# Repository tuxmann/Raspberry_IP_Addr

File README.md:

# Raspberry Pi IP Address Display

A hardware add-on that displays your Raspberry Pi's IP address on a 3-digit 7-segment LED display. Compatible with all Raspberry Pi models and other pin-compatible SBCs (Orange Pi, Banana Pi, Odroid, etc.).

## Quick Start

1. **Enable I2C and SPI:** `sudo raspi-config` → Interface Options
2. **Install:** `sudo apt install python3-smbus i2c-tools` (or `pip install smbus2`)
3. **Run:** `python3 hostip.py`
4. **Auto-start at boot:** `./deploy-to-pi.sh --install-service` (after deploying)

See **[docs/SETUP.md](docs/SETUP.md)** for the full setup guide, including ATtiny88 programming and the reset pin requirement.

## Hardware

- **Board:** ATtiny88 drives a 3-digit ELT-316 common-anode 7-segment display
- **Communication:** I2C at address 0x5A
- **Size:** Sits 0.6" (1.5cm) above the Pi; total height ~1" (2.5cm) with headers
- **Expansion:** P3 (left) and P4 (right) connectors bring out Port C & D (ADC, analog comparator, external interrupts)

## Features

- Power-on message ("rPI IP by JAY v1.1 GPL 3")
- Timeout message if no IP received within ~5 minutes
- Cycles through IP octets (e.g., 192 → 168 → 1 → 100)

## Climate node (DHT22, standalone)

The board can run **without a Pi** as a temperature/humidity display using a **DHT22** on header **P3 pin 1 (PC0)**.

- Firmware: [`climate-node-dht22/`](climate-node-dht22/)
- Setup, wiring, build, and flash: **[docs/CLIMATE_NODE.md](docs/CLIMATE_NODE.md)**

Shows °F (e.g. `78.3`) and humidity (e.g. `H38`), one sensor read every 6 seconds (3 s per value on the display). Optional photoresistor dimming on **P3 pin 2**; compile-time calibration offsets for temperature and humidity.

## Documentation

- [Setup Guide](docs/SETUP.md) — Pi IP display: installation, configuration, and flashing
- [Climate Node (DHT22)](docs/CLIMATE_NODE.md) — Standalone temp/humidity firmware
- [Releases](https://github.com/tuxmann/Raspberry_IP_Addr/releases) — Pre-built binaries and documents
- [Schematic](docs/Pi.IP.Addr.Schematic.pdf)

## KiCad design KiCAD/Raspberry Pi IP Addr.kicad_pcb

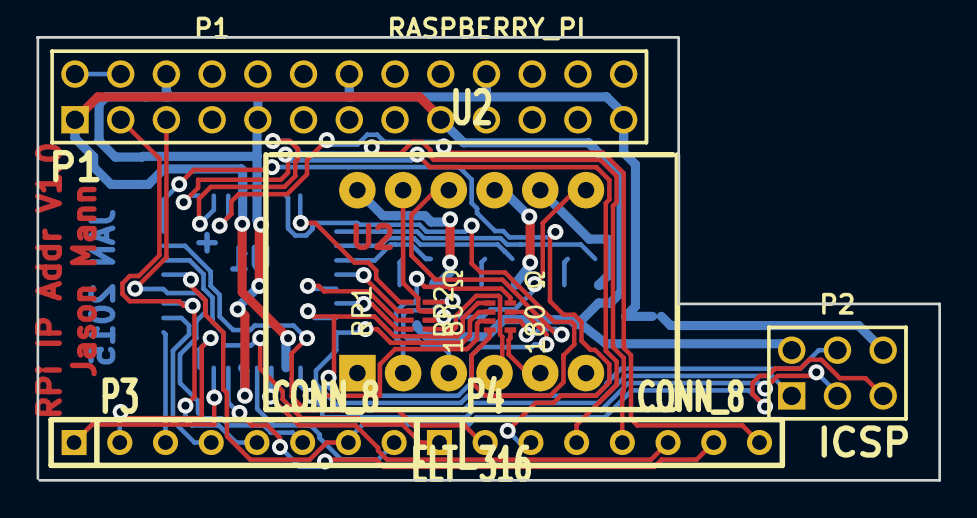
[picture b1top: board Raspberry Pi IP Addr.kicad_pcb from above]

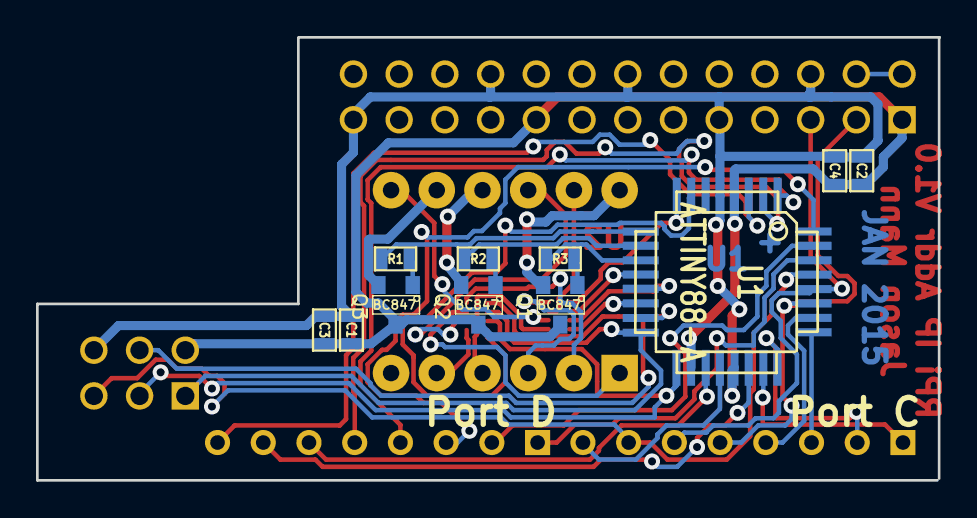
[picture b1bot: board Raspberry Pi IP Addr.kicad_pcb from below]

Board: 2 copper layers, 50.1 x 24.6 mm, 18 parts (11 on the bottom side), 44 nets.

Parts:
C1, C2, C3, C4: 100nF; SM0603
P1: RASPBERRY_PI; pin_array_13x2
P2: CONN_3X2; pin_array_3x2
P3, P4: CONN_8; SIL-8
Q1, Q2, Q3: BC847; SOT23
R1, R2, R3: 10k Ω; SM0603
RP1, RP2: 180 Ω; Res_0402x4
U1: ATTINY88-A; TQFP32
U2: ELT-316; ELD-316

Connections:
3.3VDC: C1.1, C2.1, C3.1, C4.1, P1.1, P1.17, P2.2, Q1.3, Q2.3, Q3.3, U1.4, U1.18
5VDC: P1.2, P1.4
GND: C1.2, C2.2, C3.2, C4.2, P1.6, P1.9, P1.14, P1.20, P1.25, P2.6, U1.5, U1.21
LED_D1: R3.1, U1.11
LED_D2: R2.1, U1.10
LED_D3: R1.1, U1.9
LED_DP: RP1.1, U1.8
LED_a: RP1.2, U1.12
LED_b: RP1.3, U1.13
LED_c: RP1.4, U1.14
LED_d: P2.4, RP2.1, U1.15
LED_e: P2.1, RP2.2, U1.16
LED_f: P2.3, RP2.3, U1.17
LED_g: RP2.4, U1.7
unnamed: Q1.2, U2.12
unnamed: Q2.2, U2.9
unnamed: Q3.2, U2.8
unnamed: Q3.1, R1.2
unnamed: Q1.1, R3.2
unnamed: Q2.1, R2.2
unnamed: P3.3, U1.25
unnamed: P3.2, U1.24
unnamed: P3.1, U1.23
unnamed: P3.8, U1.20
unnamed: P3.4, U1.26
unnamed: P4.5, U1.2
unnamed: P4.4, U1.1
unnamed: P4.3, U1.32
unnamed: P4.2, U1.31
unnamed: P4.1, U1.30
unnamed: RP1.8, U2.3
unnamed: RP2.5, U2.5
unnamed: RP2.6, U2.10
unnamed: RP2.7, U2.1
unnamed: RP2.8, U2.2
unnamed: RP1.7, U2.11
unnamed: RP1.6, U2.7
unnamed: RP1.5, U2.4
PA0: P4.6, U1.19
PA1: P4.7, U1.22
PA2: P4.8, U1.3
RESET: P2.5, P3.7, U1.29
SCL: P1.5, P3.6, U1.28
SDA: P1.3, P3.5, U1.27

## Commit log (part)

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2015-02-17 Create show_ip.c
    Updates will be made this week to improve timing
2015-02-17 Create hostip.py
    Needs cleanup. I will work on cleaning up the code this week to make it persistent and try to find a better solution to write_i2c_block_data.
2015-02-24 Condensed code, added missing IP error handling.
    Condensed code. Python script now sends 255.0.255.0 to the add-on board when no IP address is detected. Once the it is reconnected with the network, the new IP address is sent to the add-on board.
2015-03-01 Change the refresh time
    Changed the refresh time to 2 minutes instead of 10 seconds to send new data to the add-on board less often.
2015-03-03 Fixed a coding mistake.
    Changed sleep time from 5 to refresh constant
2015-03-06 Speed up octet cycling
    Octet cycling was too long. I cut the duration times in half.
2015-03-11 Added explicit GPLV3 license statement
2015-03-11 Changed GPLV2 to GPLV3
2015-03-11 Remove comments that don't matter to the code.
2015-03-11 Show_pi.c count down
    This program proves that the Pi IP Address board was reprogrammed. If it is programmed, the numbers will count down (4,3,2,1) instead of counting up. The IP address will still display the same.
2015-03-14 Happy Pi Day! 3.14
    Very simple and inefficient code to display "HAP PY PI DAY 3.14"
2016-02-11 Correcting IPv6 failures
    I have updated the code because hostname -I caused the script to fail if non-integers were detected in the line. The new way is more robust.
2016-02-27 Corrected Typo
    Changed Most to Least
2016-04-14 Added a way to determine the I2C port
    I included the ability to query the possible I2C ports and see if the Pi IP Address board responds. If it responds, then the I2C port number is assigned.
2016-04-14 Create a cleaner exit when Pi IP board is missing
2016-08-19 Added additional features
    Updated the version to 1.1. The IP address module now displays a power on message and funny timeout message. Additional comments to the code were added for clarity.
2018-11-07 Converted script to Python3
    removed python 2 parts of the script and replaced them with python 3. Also made the script more concise and less redundant.
2018-11-08 Correcting markdown errors
2020-12-09 Morse Code version
    This version lets you get the IP address. Just download the Morse Code Agent program and set up the script to run at start up.
